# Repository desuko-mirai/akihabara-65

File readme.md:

# Akihabara 65 v0.4

### A 65% keyboard designed for JIS layout, with ANSI and ISO support.

## Design Overview & Features

### Case

- 7° typing angle
- Modified sandwich mount
- [Effective Keyboard Height](https://github.com/Croktopus/effective-keyboard-height): 21.9 mm
- [SKUF](https://github.com/Zambumon/SKUF) Feet
- Approximately 1050 g with aluminium plate
- Exposed plate edges
- Plate features four rows of flex cuts and four "mounting points" in an attempt to soften the harshness associated with sandwich mount
- 9.525 mm top and bottom bezels, 4.7625 mm side bezels
- 339 x 116 x 31 mm

### PCB

- Designed for STM32F072, but should be compatible with other STM32 models
- [Unified C3](https://github.com/ai03-2725/Unified-Daughterboard) Daughterboard
- QMK & VIA in progress
- PCB designed with KiCAD 6
- Bottom row legend; no more guessing where to place your switches and stabilizers
- Two flex cuts

## Layouts

The Akihabara 65 was designed for a JIS layout with a 4.5u spacebar, but it supports many layouts. Options include:

- Standard or Stepped Caps Lock
- Standard or Split Backspace
- 2.75u or Split Right Shift (1.75u | 1u **OR** 1u | 1.75u)
- ANSI or ISO/JIS Enter
- 4.5u, 6.25u, or 7u Bottom Row

## Supported Keycap Sets

Almost all sets will support ANSI, and many support ISO as well, however JIS is significantly less common amongst custom keyboard enthusiasts, even in Japan. Still, keycap sets with JIS compatibility do exist. Known sets include:

- [ePBT SimpleJA R2](https://geekhack.org/index.php?topic=114422.0)[^kitting][^spacebar] by ai03
- [ePBT ModernJA](https://geekhack.org/index.php?topic=109341.0)[^kitting][^spacebar] by ai03
- [TMT Story](https://geekhack.org/index.php?topic=112681.0)[^gb] by shawnlyx/lunasho
- [GMK JIS](https://geekhack.org/index.php?topic=108328.0)[^gb] by 2Moons
- [Majestouch Keycaps](https://www.diatec.co.jp/products/list.php?s[]=100:1002:10008)[^fn] by FILCO/DIATEC

[^kitting]: Requires JIS/ISO kit
[^spacebar]: Does not include 4.5u spacebar
[^gb]: Group buy not yet fulfilled
[^fn]: Does not inclue R4 1u Fn key; can substitute with Menu key

### 4.5u Keycaps & Stabilizers

Outside of Japan, 4.5u spacebars are very uncommon; even more so in the quality we expect in this hobby. The selection is very limited, but not completely nonexistent.

The easiest way to acquire a 4.5u spacebar is to purchase one from KPRepublic [here](https://kprepublic.com/products/xda-blank-convex-spacebar-grey-1-75u-2u-2-25u-2-75u-3u-4-5u-5-5u-6u-6-25u-6-5u-7u-blank-keycaps-for-xd60-xd64-xd84-xd75-gh60-60). Unfortunately, these only come in grey PBT in XDA profile. An XDA spacebar does not look too out of place amongst Cherry-profile keycaps, and being PBT you can theoretically dye it. Signature Plastics also produces 4.5u spacebars in their SA profile, but these are unfortunately not sold on PMK, so acquiring one might prove difficult. TomatoCaps has a 4.5u spacebar mold, as seen in TMT Story. GMK will also have a 4.5u spacebar mold some time in 2022.

The only place I have found that sells 4.5u stabilizers is NPKC RGB CP Store on AliExpress. I purchased mine from their store [here](https://www.aliexpress.com/item/32855603554.html); just leave the seller a message on checkout saying you want 4.5u wires instead of 6.25u. I believe they will also sell you the wires by themselves; the housings are not very good at all, so this route may be preferable.

You can also make a 4.5u wire yourself by cutting and bending a 6.25u or 7u wire (or any wire longer than 4.5u). The centre-to-centre distance of the stabilizer mounts on a 4.5u spacebar is 69.342 mm. It is difficult to get the bend radius tight without a wire bender, but that still did not cause any issues with the Durock wire I bent.

## And A Big "Thank You" To:

- **kkatano** for the [Bakeneko](https://github.com/kkatano/bakeneko-65), from which I took many design elements for the case (and it's also just a really nice keyboard)
- **4pplet** and **Gondolindrim** for sharing their knowledge of ARM-powered keyboards in a world filled with AVR
- **ai03** for their brilliant [plate generator](https://kbplate.ai03.com/) and [keyswitch footprints](https://github.com/ai03-2725/MX_Alps_Hybrid), as well as their [PCB design guide](https://wiki.ai03.com/books/pcb-design)
- **hadi** for their [PCB design series](https://www.youtube.com/watch?v=BhFqkVggv8Q), unfinished as it may be
- **2Moons** for helping me confirm dimensions for 4.5u spacebars

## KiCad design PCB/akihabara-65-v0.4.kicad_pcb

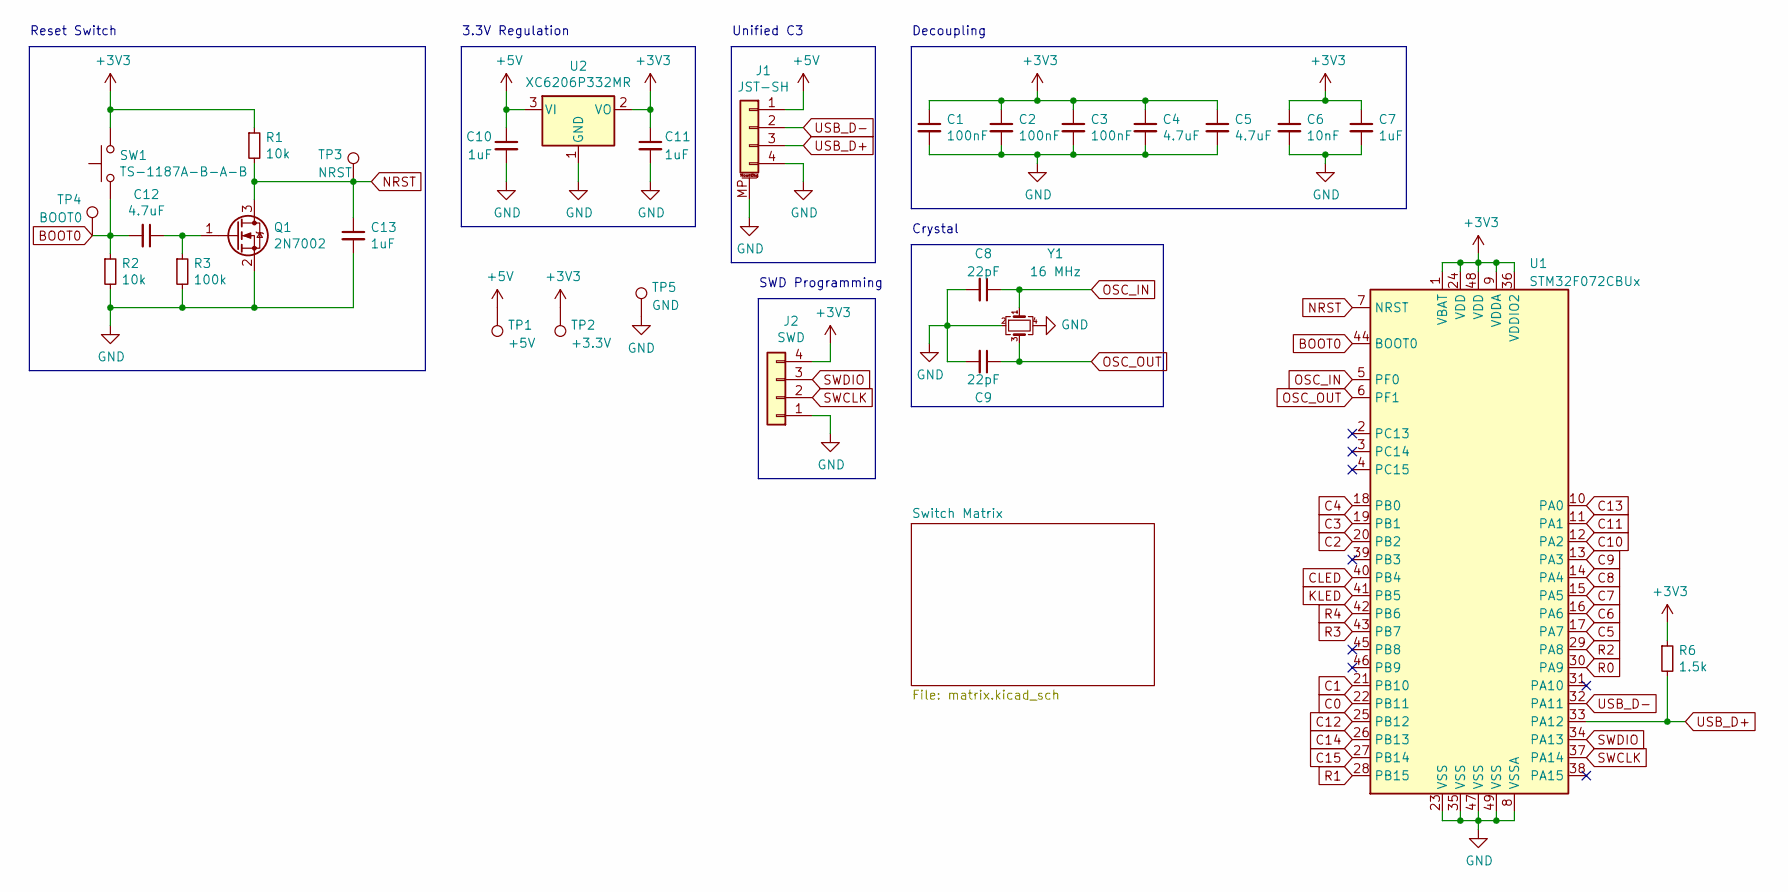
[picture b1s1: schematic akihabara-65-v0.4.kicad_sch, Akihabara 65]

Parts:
C1, C2, C3: 100nF; C_0805_2012Metric; LCSC C28233
C4, C5, C12: 4.7uF; C_0805_2012Metric; LCSC C1779
C6: 10nF; C_0805_2012Metric; LCSC C1710
C7, C10, C11, C13: 1uF; C_0805_2012Metric; LCSC C28323
C8, C9: 22pF; C_0805_2012Metric; LCSC C1804
J1: JST-SH; JST_SH_SM04B-SRSS-TB_1x04-1MP_P1.00mm_Horizontal; LCSC C160404
J2: SWD; PinHeader_1x04_P2.54mm_Vertical
Q1: 2N7002; SOT-23; LCSC C8545
R1, R2: 10k; R_0805_2012Metric; LCSC C17414
R3: 100k; R_0805_2012Metric; LCSC C17407
R6: 1.5k; R_0805_2012Metric; LCSC C4310
SW1: TS-1187A-B-A-B; SW_SPST_TL3342; LCSC C318884
TP1: +5V; TestPoint_Pad_1.0x1.0mm
TP2: +3.3V; TestPoint_Pad_1.0x1.0mm
TP3: NRST; TestPoint_Pad_1.0x1.0mm
TP4: BOOT0; TestPoint_Pad_1.0x1.0mm
TP5: GND; TestPoint_Pad_1.0x1.0mm
U1: STM32F072CBUx; STM32_CxT_CxU_Hybrid; LCSC C92504
U2: XC6206P332MR; SOT-23; LCSC C5446
Y1: 16 MHz; Crystal_SMD_3225-4Pin_3.2x2.5mm; LCSC C13738

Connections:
+3V3: C1.1, C2.1, C3.1, C4.1, C5.1, C6.1, C7.1, C11.1, J2.4, R1.1, R6.1, SW1.2, TP2.1, U1.1 (VBAT), U1.9 (VDDA), U1.24 (VDD), U1.36 (VDDIO2), U1.48 (VDD), U2.2 (VO)
+5V: C10.1, J1.1, TP1.1, U2.3 (VI); also elsewhere on the board
BOOT0: C12.2, R2.1, SW1.1, TP4.1, U1.44 (BOOT0)
C0: U1.22 (PB11); also elsewhere on the board
C1: U1.21 (PB10); also elsewhere on the board
C2: U1.20 (PB2); also elsewhere on the board
C3: U1.19 (PB1); also elsewhere on the board
C4: U1.18 (PB0); also elsewhere on the board
C5: U1.17 (PA7); also elsewhere on the board
C6: U1.16 (PA6); also elsewhere on the board
C7: U1.15 (PA5); also elsewhere on the board
C8: U1.14 (PA4); also elsewhere on the board
C9: U1.13 (PA3); also elsewhere on the board
C10: U1.12 (PA2); also elsewhere on the board
C11: U1.11 (PA1); also elsewhere on the board
C12: U1.25 (PB12); also elsewhere on the board
C13: U1.10 (PA0); also elsewhere on the board
C14: U1.26 (PB13); also elsewhere on the board
C15: U1.27 (PB14); also elsewhere on the board
CLED: U1.40 (PB4); also elsewhere on the board
GND: C1.2, C2.2, C3.2, C4.2, C5.2, C6.2, C7.2, C8.2, C9.2, C10.2, C11.2, C13.2, J1.4, J1.MP (MountPin), J2.1, Q1.2 (S), R2.2, R3.2, TP5.1, U1.8 (VSSA), U1.23 (VSS), U1.35 (VSS), U1.47 (VSS), U1.49 (VSS), U2.1 (GND), Y1.2, Y1.4
KLED: U1.41 (PB5); also elsewhere on the board
NRST: C13.1, Q1.3 (D), R1.2, TP3.1, U1.7 (NRST)
unnamed: C12.1, Q1.1 (G), R3.1
OSC_IN: C8.1, U1.5 (PF0), Y1.1
OSC_OUT: C9.1, U1.6 (PF1), Y1.3
R0: U1.30 (PA9); also elsewhere on the board
R1: U1.28 (PB15); also elsewhere on the board
R2: U1.29 (PA8); also elsewhere on the board
R3: U1.43 (PB7); also elsewhere on the board
R4: U1.42 (PB6); also elsewhere on the board
SWCLK: J2.2, U1.37 (PA14)
SWDIO: J2.3, U1.34 (PA13)
USB_D+: J1.3, R6.2, U1.33 (PA12)
USB_D-: J1.2, U1.32 (PA11)

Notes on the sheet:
Reset Switch
3.3V Regulation
SWD Programming
Decoupling
Crystal
Unified C3

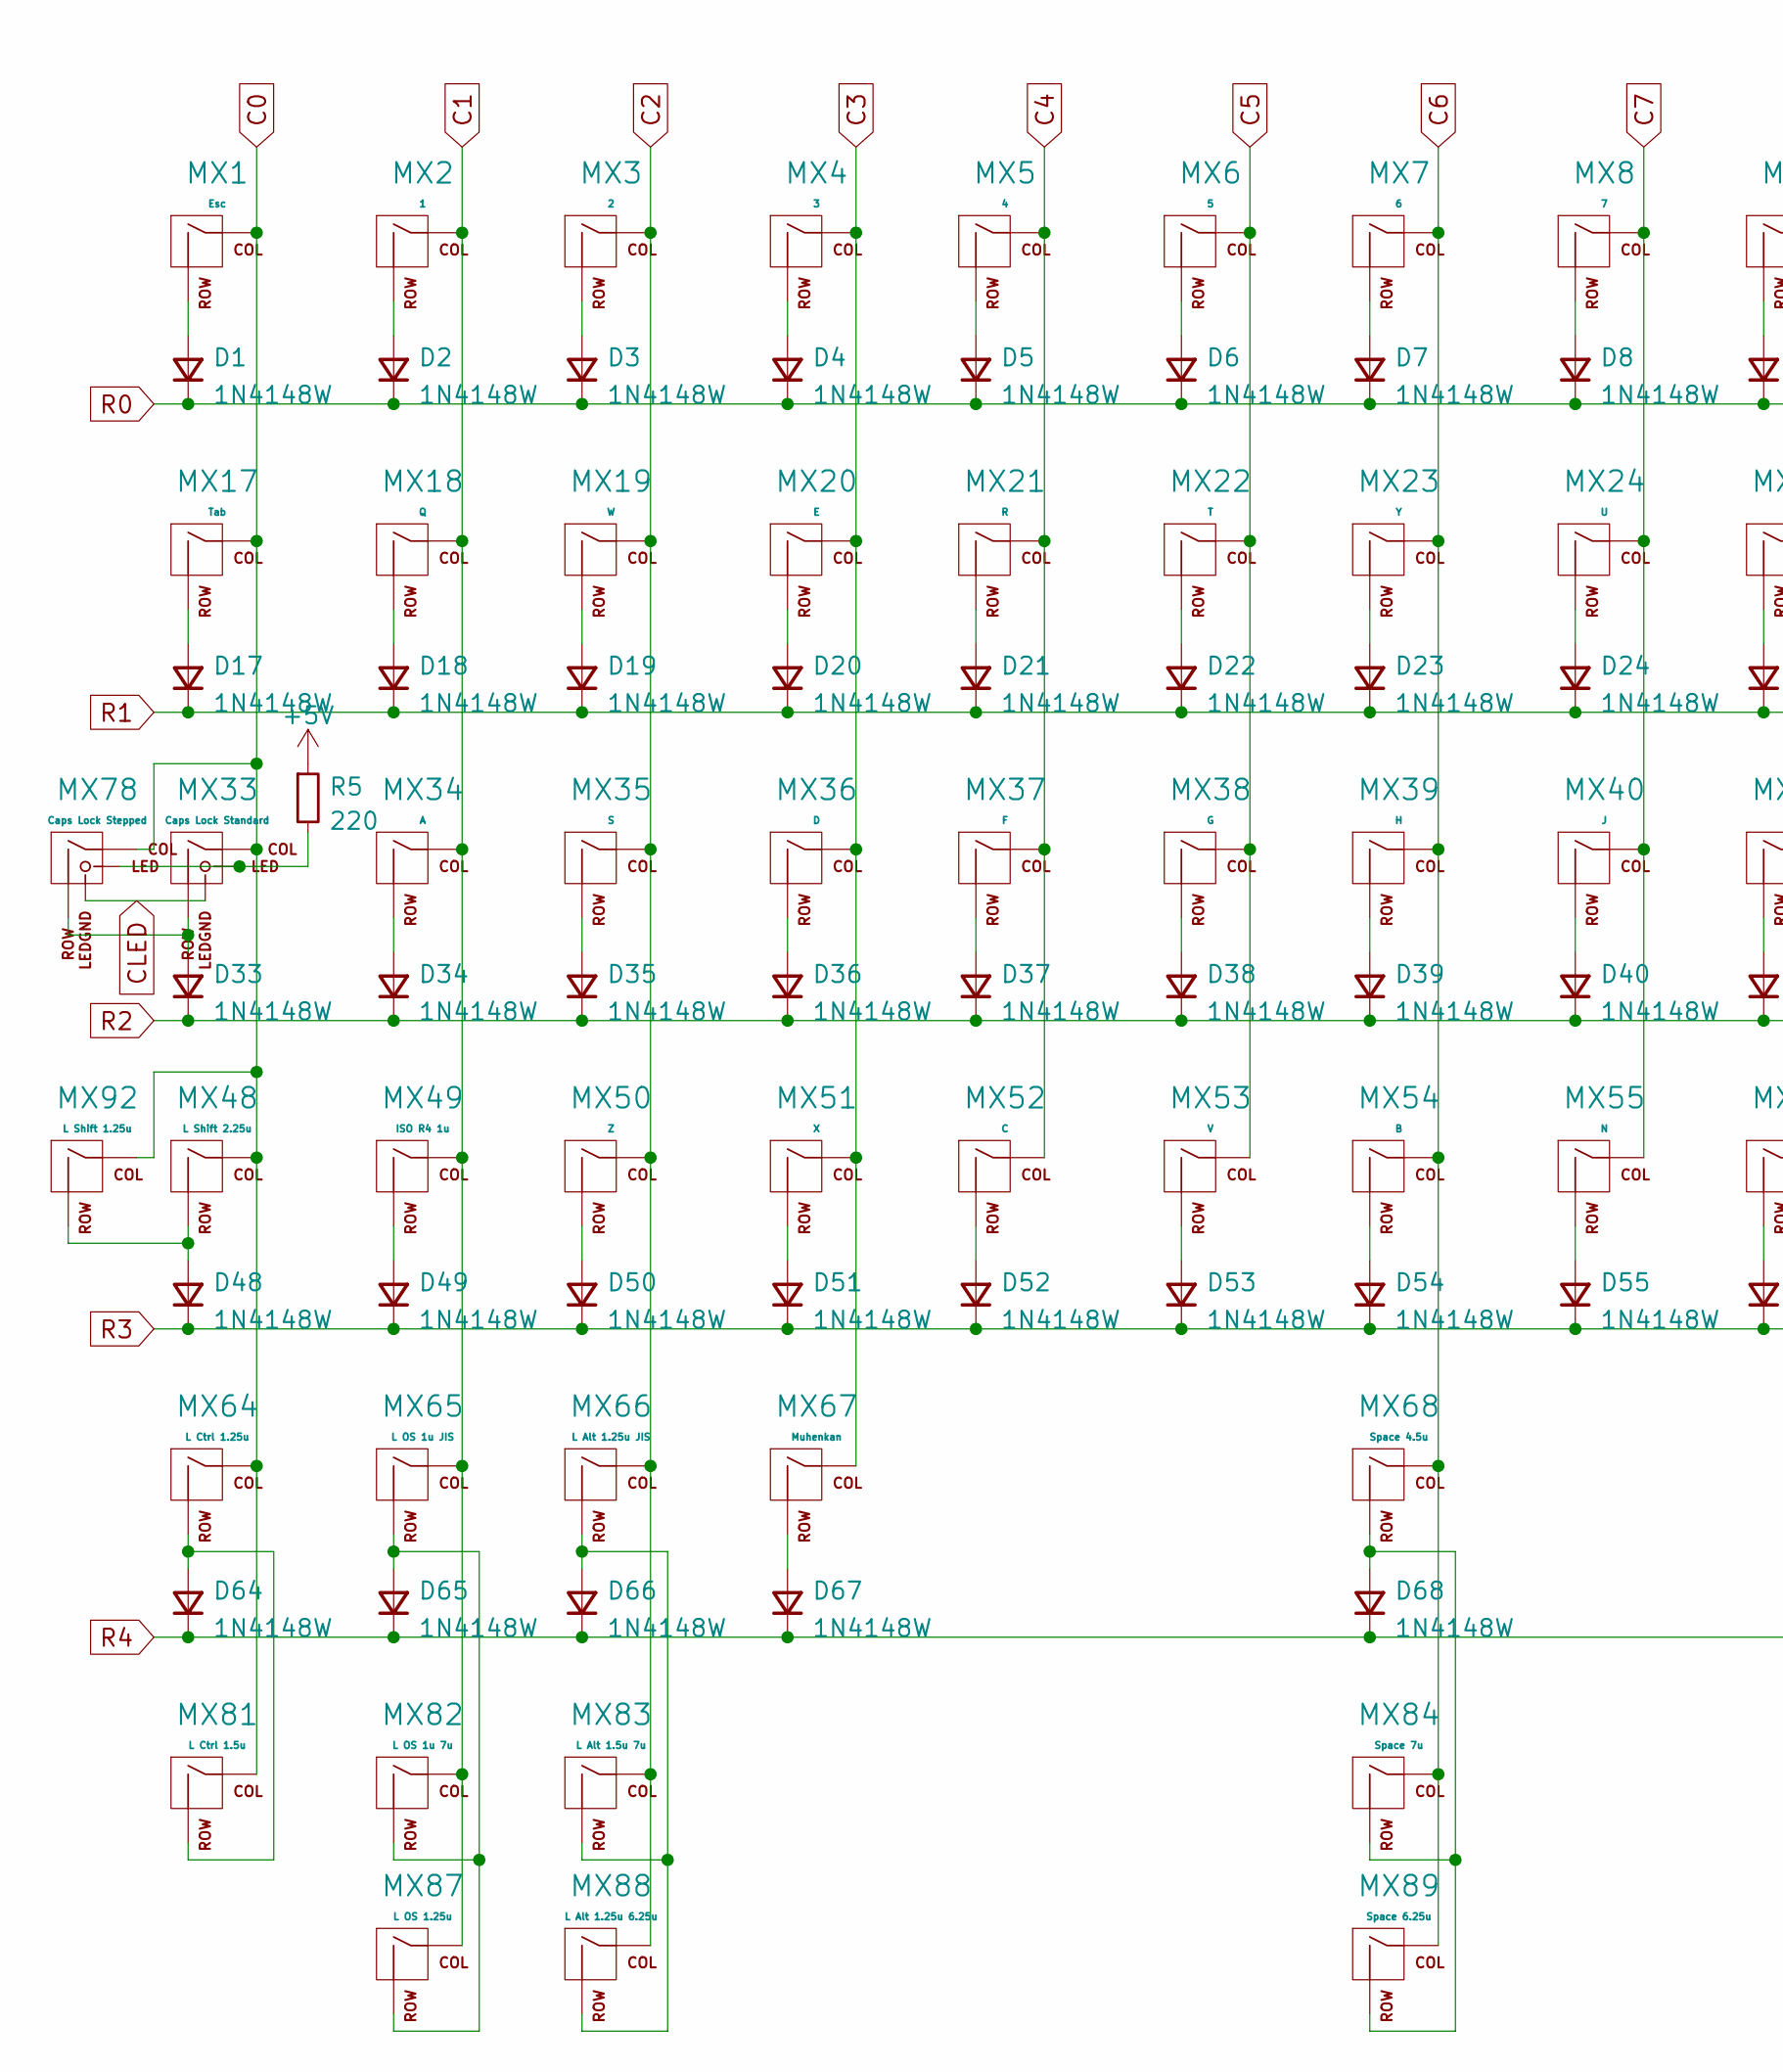
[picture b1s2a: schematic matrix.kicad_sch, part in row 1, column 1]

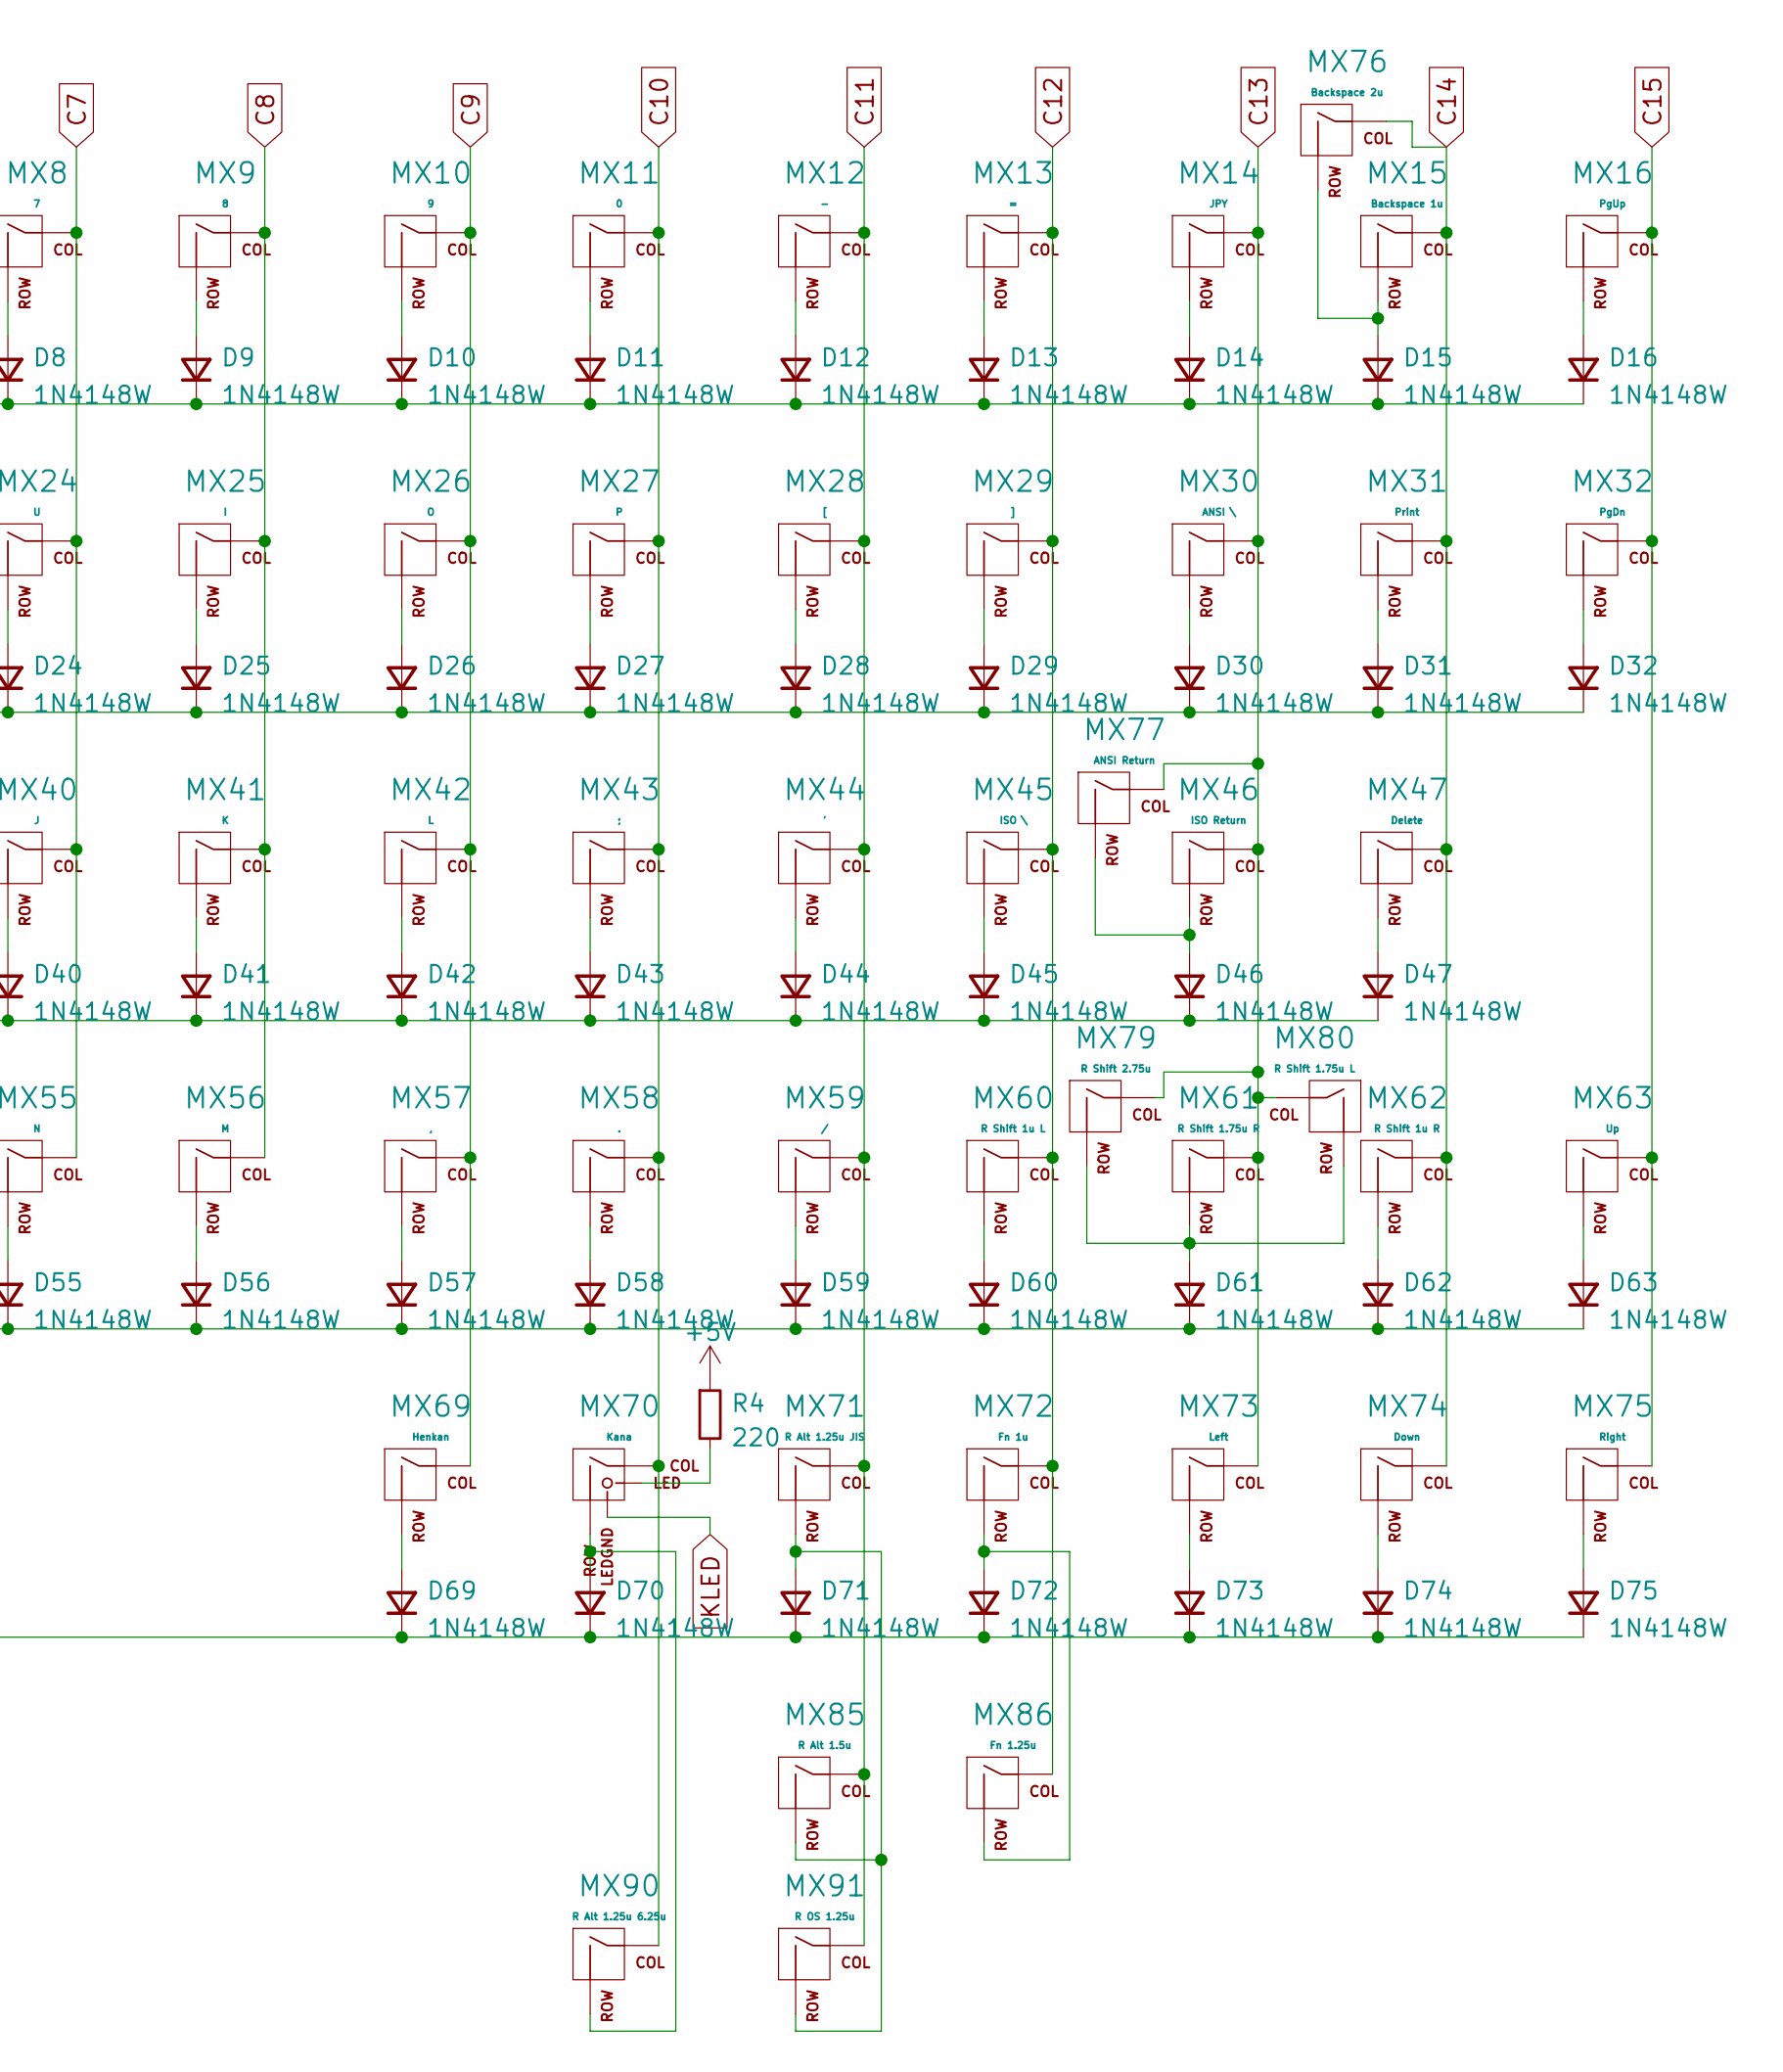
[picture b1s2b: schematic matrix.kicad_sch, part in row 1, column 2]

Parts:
D1, D2, D3, D4, D5, D6, D7, D8, D9, D10, D11, D12, D13, D14, D15, D16, D17, D18, D19, D20, D21, D22, D23, D24, D25, D26, D27, D28, D29, D30, D31, D32, D33, D34, D35, D36, D37, D38, D39, D40, D41, D42, D43, D44, D45, D46, D47, D48, D49, D50, D51, D52, D53, D54, D55, D56, D57, D58, D59, D60, D61, D62, D63, D64, D65, D66, D67, D68, D69, D70, D71, D72, D73, D74, D75: 1N4148W; D_SOD-123; LCSC C81598
MX1: Esc; MXOnly-1U-NoLED
MX2: 1; MXOnly-1U-NoLED
MX3: 2; MXOnly-1U-NoLED
MX4: 3; MXOnly-1U-NoLED
MX5: 4; MXOnly-1U-NoLED
MX6: 5; MXOnly-1U-NoLED
MX7: 6; MXOnly-1U-NoLED
MX8: 7; MXOnly-1U-NoLED
MX9: 8; MXOnly-1U-NoLED
MX10: 9; MXOnly-1U-NoLED
MX11: 0; MXOnly-1U-NoLED
MX12: -; MXOnly-1U-NoLED
MX13: =; MXOnly-1U-NoLED
MX14: JPY; MXOnly-1U-NoLED
MX15: Backspace 1u; MXOnly-1U-NoLED
MX16: PgUp; MXOnly-1U-NoLED
MX17: Tab; MXOnly-1.5U-NoLED
MX18: Q; MXOnly-1U-NoLED
MX19: W; MXOnly-1U-NoLED
MX20: E; MXOnly-1U-NoLED
MX21: R; MXOnly-1U-NoLED
MX22: T; MXOnly-1U-NoLED
MX23: Y; MXOnly-1U-NoLED
MX24: U; MXOnly-1U-NoLED
MX25: I; MXOnly-1U-NoLED
MX26: O; MXOnly-1U-NoLED
MX27: P; MXOnly-1U-NoLED
MX28: [; MXOnly-1U-NoLED
MX29: ]; MXOnly-1U-NoLED
MX30: ANSI \; MXOnly-1.5U-NoLED
MX31: Print; MXOnly-1U-NoLED
MX32: PgDn; MXOnly-1U-NoLED
MX33: Caps Lock Standard; MXOnly-1.75U
MX34: A; MXOnly-1U-NoLED
MX35: S; MXOnly-1U-NoLED
MX36: D; MXOnly-1U-NoLED
MX37: F; MXOnly-1U-NoLED
MX38: G; MXOnly-1U-NoLED
MX39: H; MXOnly-1U-NoLED
MX40: J; MXOnly-1U-NoLED
MX41: K; MXOnly-1U-NoLED
MX42: L; MXOnly-1U-NoLED
MX43: ;; MXOnly-1U-NoLED
MX44: '; MXOnly-1U-NoLED
MX45: ISO \; MXOnly-1U-NoLED
MX46: ISO Return; MXOnly-ISO-ROTATED-ReversedStabilizers-NoLED
MX47: Delete; MXOnly-1U-NoLED
MX48: L Shift 2.25u; MXOnly-2.25U-NoLED
MX49: ISO R4 1u; MXOnly-1U-NoLED
MX50: Z; MXOnly-1U-NoLED
MX51: X; MXOnly-1U-NoLED
MX52: C; MXOnly-1U-NoLED
MX53: V; MXOnly-1U-NoLED
MX54: B; MXOnly-1U-NoLED
MX55: N; MXOnly-1U-NoLED
MX56: M; MXOnly-1U-NoLED
MX57: ,; MXOnly-1U-NoLED
MX58: .; MXOnly-1U-NoLED
MX59: /; MXOnly-1U-NoLED
MX60: R Shift 1u L; MXOnly-1U-NoLED
MX61: R Shift 1.75u R; MXOnly-1.75U-NoLED
MX62: R Shift 1u R; MXOnly-1U-NoLED
MX63: Up; MXOnly-1U-NoLED
MX64: L Ctrl 1.25u; MXOnly-1.25U-NoLED
MX65: L OS 1u JIS; MXOnly-1U-NoLED
MX66: L Alt 1.25u JIS; MXOnly-1.25U-NoLED
MX67: Muhenkan; MXOnly-1U-NoLED
MX68: Space 4.5u; MXOnly-4.5U-ReversedStabilizers-NoLED
MX69: Henkan; MXOnly-1.25U-NoLED
MX70: Kana; MXOnly-1.25U
MX71: R Alt 1.25u JIS; MXOnly-1.25U-NoLED
MX72: Fn 1u; MXOnly-1U-NoLED
MX73: Left; MXOnly-1U-NoLED
MX74: Down; MXOnly-1U-NoLED
MX75: Right; MXOnly-1U-NoLED
MX76: Backspace 2u; MXOnly-2U-NoLED
MX77: ANSI Return; MXOnly-2.25U-ReversedStabilizers-NoLED
MX78: Caps Lock Stepped; MXOnly-1.75U-STEPPED
MX79: R Shift 2.75u; MXOnly-2.75U-NoLED
MX80: R Shift 1.75u L; MXOnly-1.75U-NoLED
MX81: L Ctrl 1.5u; MXOnly-1.5U-NoLED
MX82: L OS 1u 7u; MXOnly-1U-NoLED
MX83: L Alt 1.5u 7u; MXOnly-1.5U-NoLED
MX84: Space 7u; MXOnly-7U-ReversedStabilizers-NoLED
MX85: R Alt 1.5u; MXOnly-1.5U-NoLED
MX86: Fn 1.25u; MXOnly-1.25U-NoLED
MX87: L OS 1.25u; MXOnly-1.25U-NoLED
MX88: L Alt 1.25u 6.25u; MXOnly-1.25U-NoLED
MX89: Space 6.25u; MXOnly-6.25U-ReversedStabilizers-NoLED
MX90: R Alt 1.25u 6.25u; MXOnly-1.25U-NoLED
MX91: R OS 1.25u; MXOnly-1.25U-NoLED
MX92: L Shift 1.25u; MXOnly-1.25U-NoLED
R4, R5: 220; R_0805_2012Metric; LCSC C17557

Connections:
+5V: R4.1, R5.1; also elsewhere on the board
C0: MX1.1 (COL), MX17.1 (COL), MX33.1 (COL), MX48.1 (COL), MX64.1 (COL), MX78.1 (COL), MX81.1 (COL), MX92.1 (COL); also elsewhere on the board
C1: MX2.1 (COL), MX18.1 (COL), MX34.1 (COL), MX49.1 (COL), MX65.1 (COL), MX82.1 (COL), MX87.1 (COL); also elsewhere on the board
C2: MX3.1 (COL), MX19.1 (COL), MX35.1 (COL), MX50.1 (COL), MX66.1 (COL), MX83.1 (COL), MX88.1 (COL); also elsewhere on the board
C3: MX4.1 (COL), MX20.1 (COL), MX36.1 (COL), MX51.1 (COL), MX67.1 (COL); also elsewhere on the board
C4: MX5.1 (COL), MX21.1 (COL), MX37.1 (COL), MX52.1 (COL); also elsewhere on the board
C5: MX6.1 (COL), MX22.1 (COL), MX38.1 (COL), MX53.1 (COL); also elsewhere on the board
C6: MX7.1 (COL), MX23.1 (COL), MX39.1 (COL), MX54.1 (COL), MX68.1 (COL), MX84.1 (COL), MX89.1 (COL); also elsewhere on the board
C7: MX8.1 (COL), MX24.1 (COL), MX40.1 (COL), MX55.1 (COL); also elsewhere on the board
C8: MX9.1 (COL), MX25.1 (COL), MX41.1 (COL), MX56.1 (COL); also elsewhere on the board
C9: MX10.1 (COL), MX26.1 (COL), MX42.1 (COL), MX57.1 (COL), MX69.1 (COL); also elsewhere on the board
C10: MX11.1 (COL), MX27.1 (COL), MX43.1 (COL), MX58.1 (COL), MX70.1 (COL), MX90.1 (COL); also elsewhere on the board
C11: MX12.1 (COL), MX28.1 (COL), MX44.1 (COL), MX59.1 (COL), MX71.1 (COL), MX85.1 (COL), MX91.1 (COL); also elsewhere on the board
C12: MX13.1 (COL), MX29.1 (COL), MX45.1 (COL), MX60.1 (COL), MX72.1 (COL), MX86.1 (COL); also elsewhere on the board
C13: MX14.1 (COL), MX30.1 (COL), MX46.1 (COL), MX61.1 (COL), MX73.1 (COL), MX77.1 (COL), MX79.1 (COL), MX80.1 (COL); also elsewhere on the board
C14: MX15.1 (COL), MX31.1 (COL), MX47.1 (COL), MX62.1 (COL), MX74.1 (COL), MX76.1 (COL); also elsewhere on the board
C15: MX16.1 (COL), MX32.1 (COL), MX63.1 (COL), MX75.1 (COL); also elsewhere on the board
CLED: MX33.4 (LEDGND), MX78.4 (LEDGND); also elsewhere on the board
KLED: MX70.4 (LEDGND); also elsewhere on the board
unnamed: D1.2 (A), MX1.2 (ROW)
unnamed: D2.2 (A), MX2.2 (ROW)
unnamed: D3.2 (A), MX3.2 (ROW)
unnamed: D4.2 (A), MX4.2 (ROW)
unnamed: D5.2 (A), MX5.2 (ROW)
unnamed: D6.2 (A), MX6.2 (ROW)
unnamed: D7.2 (A), MX7.2 (ROW)
unnamed: D8.2 (A), MX8.2 (ROW)
unnamed: D9.2 (A), MX9.2 (ROW)
unnamed: D10.2 (A), MX10.2 (ROW)
unnamed: D11.2 (A), MX11.2 (ROW)
unnamed: D12.2 (A), MX12.2 (ROW)
unnamed: D13.2 (A), MX13.2 (ROW)
unnamed: D14.2 (A), MX14.2 (ROW)
unnamed: D15.2 (A), MX15.2 (ROW), MX76.2 (ROW)
unnamed: D16.2 (A), MX16.2 (ROW)
unnamed: D17.2 (A), MX17.2 (ROW)
unnamed: D18.2 (A), MX18.2 (ROW)
unnamed: D19.2 (A), MX19.2 (ROW)
unnamed: D20.2 (A), MX20.2 (ROW)
unnamed: D21.2 (A), MX21.2 (ROW)
unnamed: D22.2 (A), MX22.2 (ROW)
unnamed: D23.2 (A), MX23.2 (ROW)
unnamed: D24.2 (A), MX24.2 (ROW)
unnamed: D25.2 (A), MX25.2 (ROW)
unnamed: D26.2 (A), MX26.2 (ROW)
unnamed: D27.2 (A), MX27.2 (ROW)
unnamed: D28.2 (A), MX28.2 (ROW)
unnamed: D29.2 (A), MX29.2 (ROW)
unnamed: D30.2 (A), MX30.2 (ROW)
unnamed: D31.2 (A), MX31.2 (ROW)
unnamed: D32.2 (A), MX32.2 (ROW)
unnamed: D33.2 (A), MX33.2 (ROW), MX78.2 (ROW)
unnamed: D34.2 (A), MX34.2 (ROW)
unnamed: D35.2 (A), MX35.2 (ROW)
unnamed: D36.2 (A), MX36.2 (ROW)
unnamed: D37.2 (A), MX37.2 (ROW)
unnamed: D38.2 (A), MX38.2 (ROW)
unnamed: D39.2 (A), MX39.2 (ROW)
unnamed: D40.2 (A), MX40.2 (ROW)
unnamed: D41.2 (A), MX41.2 (ROW)
unnamed: D42.2 (A), MX42.2 (ROW)
unnamed: D43.2 (A), MX43.2 (ROW)
unnamed: D44.2 (A), MX44.2 (ROW)
unnamed: D45.2 (A), MX45.2 (ROW)
unnamed: D46.2 (A), MX46.2 (ROW), MX77.2 (ROW)
unnamed: D47.2 (A), MX47.2 (ROW)
unnamed: D48.2 (A), MX48.2 (ROW), MX92.2 (ROW)
unnamed: D49.2 (A), MX49.2 (ROW)
unnamed: D50.2 (A), MX50.2 (ROW)
unnamed: D51.2 (A), MX51.2 (ROW)
unnamed: D52.2 (A), MX52.2 (ROW)
unnamed: D53.2 (A), MX53.2 (ROW)
unnamed: D54.2 (A), MX54.2 (ROW)
unnamed: D55.2 (A), MX55.2 (ROW)
unnamed: D56.2 (A), MX56.2 (ROW)
unnamed: D57.2 (A), MX57.2 (ROW)
unnamed: D58.2 (A), MX58.2 (ROW)
unnamed: D59.2 (A), MX59.2 (ROW)
unnamed: D60.2 (A), MX60.2 (ROW)
unnamed: D61.2 (A), MX61.2 (ROW), MX79.2 (ROW), MX80.2 (ROW)
unnamed: D62.2 (A), MX62.2 (ROW)
unnamed: D63.2 (A), MX63.2 (ROW)
unnamed: D64.2 (A), MX64.2 (ROW), MX81.2 (ROW)
unnamed: D65.2 (A), MX65.2 (ROW), MX82.2 (ROW), MX87.2 (ROW)
unnamed: D66.2 (A), MX66.2 (ROW), MX83.2 (ROW), MX88.2 (ROW)
unnamed: D67.2 (A), MX67.2 (ROW)
unnamed: D68.2 (A), MX68.2 (ROW), MX84.2 (ROW), MX89.2 (ROW)
unnamed: D69.2 (A), MX69.2 (ROW)
unnamed: D70.2 (A), MX70.2 (ROW), MX90.2 (ROW)
unnamed: D71.2 (A), MX71.2 (ROW), MX85.2 (ROW), MX91.2 (ROW)
unnamed: D72.2 (A), MX72.2 (ROW), MX86.2 (ROW)
unnamed: D73.2 (A), MX73.2 (ROW)
unnamed: D74.2 (A), MX74.2 (ROW)
unnamed: D75.2 (A), MX75.2 (ROW)
unnamed: MX33.3 (LED), MX78.3 (LED), R5.2
unnamed: MX70.3 (LED), R4.2
R0: D1.1 (K), D2.1 (K), D3.1 (K), D4.1 (K), D5.1 (K), D6.1 (K), D7.1 (K), D8.1 (K), D9.1 (K), D10.1 (K), D11.1 (K), D12.1 (K), D13.1 (K), D14.1 (K), D15.1 (K), D16.1 (K); also elsewhere on the board
R1: D17.1 (K), D18.1 (K), D19.1 (K), D20.1 (K), D21.1 (K), D22.1 (K), D23.1 (K), D24.1 (K), D25.1 (K), D26.1 (K), D27.1 (K), D28.1 (K), D29.1 (K), D30.1 (K), D31.1 (K), D32.1 (K); also elsewhere on the board
R2: D33.1 (K), D34.1 (K), D35.1 (K), D36.1 (K), D37.1 (K), D38.1 (K), D39.1 (K), D40.1 (K), D41.1 (K), D42.1 (K), D43.1 (K), D44.1 (K), D45.1 (K), D46.1 (K), D47.1 (K); also elsewhere on the board
R3: D48.1 (K), D49.1 (K), D50.1 (K), D51.1 (K), D52.1 (K), D53.1 (K), D54.1 (K), D55.1 (K), D56.1 (K), D57.1 (K), D58.1 (K), D59.1 (K), D60.1 (K), D61.1 (K), D62.1 (K), D63.1 (K); also elsewhere on the board
R4: D64.1 (K), D65.1 (K), D66.1 (K), D67.1 (K), D68.1 (K), D69.1 (K), D70.1 (K), D71.1 (K), D72.1 (K), D73.1 (K), D74.1 (K), D75.1 (K); also elsewhere on the board

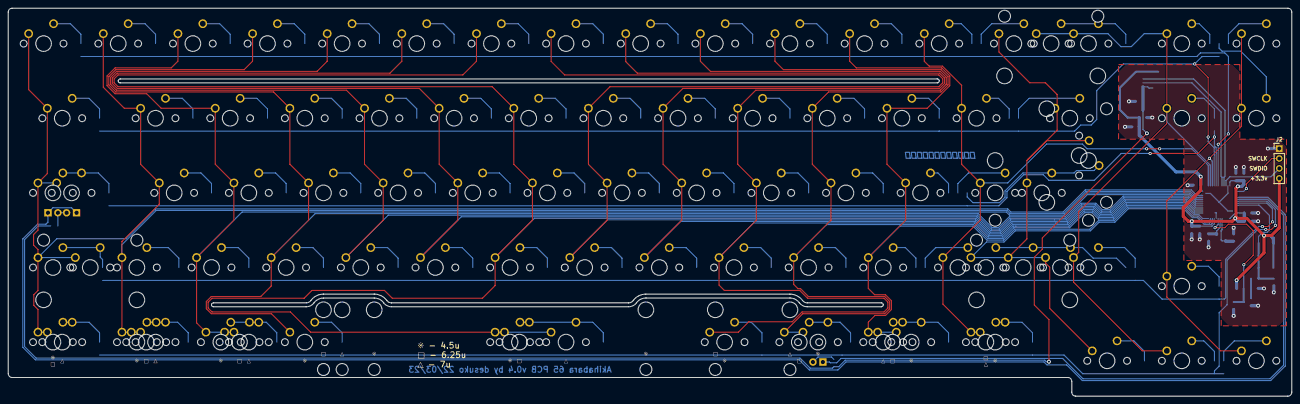
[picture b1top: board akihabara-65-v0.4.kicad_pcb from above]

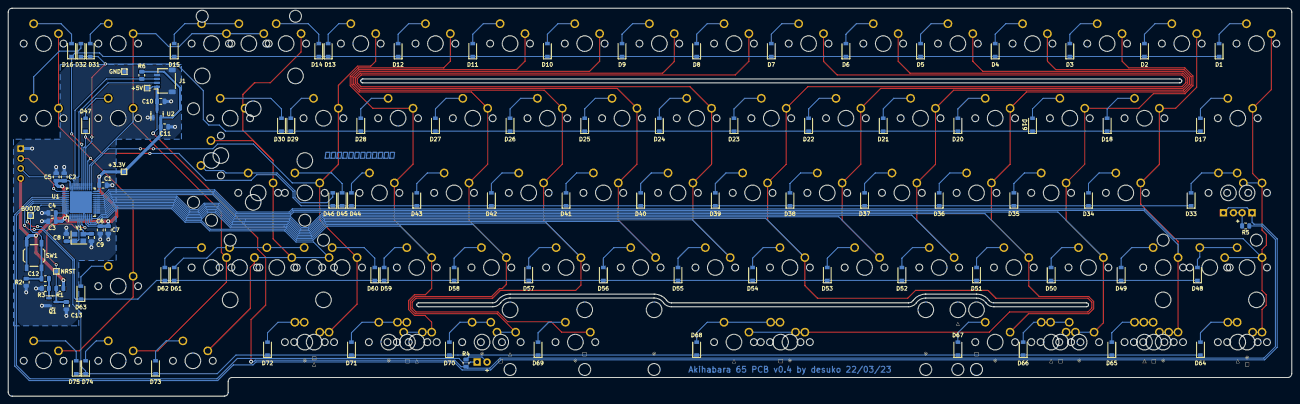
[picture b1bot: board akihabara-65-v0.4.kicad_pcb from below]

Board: 2 copper layers, 327.6 x 99.0 mm, 198 parts (105 on the bottom side), 112 nets.

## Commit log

2022-02-03 initial
2022-03-17 v4.0 Initial
2022-03-17 added images, updated readme, updated PCB
2022-03-21 add gitignore
2022-03-21 PCB update
    Added bottom row indicators on silkscreen.
2022-03-24 PCB changes, readme, case files now added
    - Changed MCU footprint from LQFP-48 to LQFP-48 + UFQFPN-48 dual footprint to combat MCU shortage
    - PCB production files are for STM32F072CBUx; edit BOM, CPL, and paste layer if you want SMT assembly for an STM32F072CBTx
    - STEP files and their associated technical drawings are now included for the case and plate
    - Added more images, updated existing images
    - Updated readme
2022-03-24 update license
    Done in order to have the license appear in the "About" section
2022-03-24 Create LICENSE
2022-03-24 update gitignore
2022-03-24 moar gitignore
2022-08-20 update PCB text
2022-08-21 edit case and add new plate
